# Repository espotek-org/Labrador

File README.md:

# What is it?
The [EspoTek Labrador](http://espotek.com/labrador) is an open-source board that turns your PC, Raspberry Pi, or Android Smartphone into a full-featured electronics lab bench, complete with oscilloscope, signal generator, and more.

This repo hosts all of the software and hardware that makes Labrador possible.

# Tutorial
If you're new to Labrador or oscilloscopes in general, I strongly recommend checking out the fantastic [tutorial series](https://www.wellys.com/posts/courses_electronics/) produced by Lief Koepsel.  It features well-written, rich articles as well as video content that explains everything more clearly than I ever could!

# Getting Started
Binary (executable) versions of the software are available for [download](https://github.com/espotek-org/Labrador/releases) for several platforms.

For the documentation, please visit the [wiki](https://github.com/espotek-org/Labrador/wiki).

## Building from Source
If you're looking to build from source but don't know where to start, Qt Creator is the easiest way to get your toes wet!  
https://www.qt.io/download-open-source/  
When installing, make sure you tick the box to install Qt 5.15 or later.
On Windows, use the MSVC2019 versions - later releases can introduce compatibility issues.

Once it's installed, open `Desktop_Interface/Labrador.pro`, then Clean All -> Run `qmake` -> Build All.

Alternatively, you can build on the command line.  The process will consist of a subset of the commands present in the build scripts in the `.github/workflows/` directory of this repo.  These are run by Github to produce the packages on the [releases page](https://github.com/espotek-org/Labrador/releases), but include app deployment commands that can be skipped for individual users.

Streamlined build scripts for individual Linux (including Raspberry Pi) and macOS users are described in the [Building the desktop interface](https://github.com/espotek-org/Labrador/wiki/Building-from-source#building-the-desktop-interface) section of the wiki.  As shown there, following installation of prerequisite packages, the Linux build simplifies to the following sequence of commands run within the `/Desktop_Interface` directory,
```
QT_SELECT=qt5 qmake
make
sudo make install
```
after which the command `labrador` launches the app.

On macOS:
```
brew install qt@5
brew install libusb
brew install eigen
brew install fftw
echo 'export PATH="/opt/homebrew/opt/qt@5/bin:$PATH"' >> ~/.zshrc

```

To build the AVR software, I use Atmel Studio 7.  Just load up the .atsln located in the `/AVR_Code` directory and push F7.  You can alternatively use open-source command-line AVR tools from GNU if you don't want to install a full IDE.  Instructions for doing so are given in the [Building the firmware](https://github.com/espotek-org/Labrador/wiki/Building-from-source#building-the-firmware) section of the wiki.  If you already have the GNU AVR tools installed, you can jump straight to the [firmware Makefile](https://github.com/espotek-org/Labrador/blob/master/AVR_Code/USB_BULK_TEST/Makefile) and start building.  The wiki includes troubleshooting tips in case you run into issues.

The PCB files can be edited in KiCAD 5.0 or later.

## Using with Nix

A `flake.nix` is provided for NixOS and Nix users:

```bash
# Build the package directly (recommended)
nix build
./result/bin/labrador

# Or enter development shell for hacking
nix develop
cd Desktop_Interface
qmake PREFIX=$PWD/_install
make -j$(nproc)
make install
./_install/bin/labrador
```

**udev rules:** To access the USB device without root, add these rules to your system. On NixOS, add to your `configuration.nix`:
```nix
services.udev.extraRules = ''
  ENV{ID_VENDOR_ID}=="03eb", ENV{ID_MODEL_ID}=="ba94", MODE="0666"
  ENV{ID_VENDOR_ID}=="03eb", ENV{ID_MODEL_ID}=="a000", MODE="0666"
  ENV{ID_VENDOR_ID}=="03eb", ENV{ID_MODEL_ID}=="2fe4", MODE="0666"
'';
```
On other distros, copy `Desktop_Interface/build_linux/69-labrador.rules` to `/etc/udev/rules.d/` and run `sudo udevadm control --reload-rules`. Unplug and replug the device after applying rules.

# Extras
There are community contributed 3D printable cases available at Thingiverse, courtesy of SpaceBex, Bostwickenator and carterw:
* https://www.thingiverse.com/thing:3188243
* https://www.thingiverse.com/thing:4705392
* https://www.thingiverse.com/thing:7400465

Dave Messink has designed [a case that can be laser cut from 3mm plywood](https://github.com/espotek-org/Labrador/files/13813693/Re__Labrador_Case.1.zip).  The [binding posts](https://www.amazon.com/dp/B07YKYP8MN) and [cables](https://www.amazon.com/dp/B08KZGPTLM) he used are from Amazon.  

# Licence
All Desktop software files are licenced under [GNU GPL v3](https://www.gnu.org/licenses/gpl.html).

All Microcontroller software files, with the exception of those provided by Atmel, are licenced under the [3-Clause BSD License](https://opensource.org/licenses/BSD-3-Clause).

All hardware files (schematics, PCB) are licenced under [Creative Commons 4.0 (CC BY-NC-SA)](https://creativecommons.org/licenses/by-nc-sa/4.0/).

# Collaboration
If you want to submit a Pull Request, bug report, or feature request, please feel free to do so here at GitHub.  
If you just want to say hello and remind me that people are actually using my product (or if you just don't want to make a GitHub account), please email admin@espotek.com

Thanks to all.  
~Chris

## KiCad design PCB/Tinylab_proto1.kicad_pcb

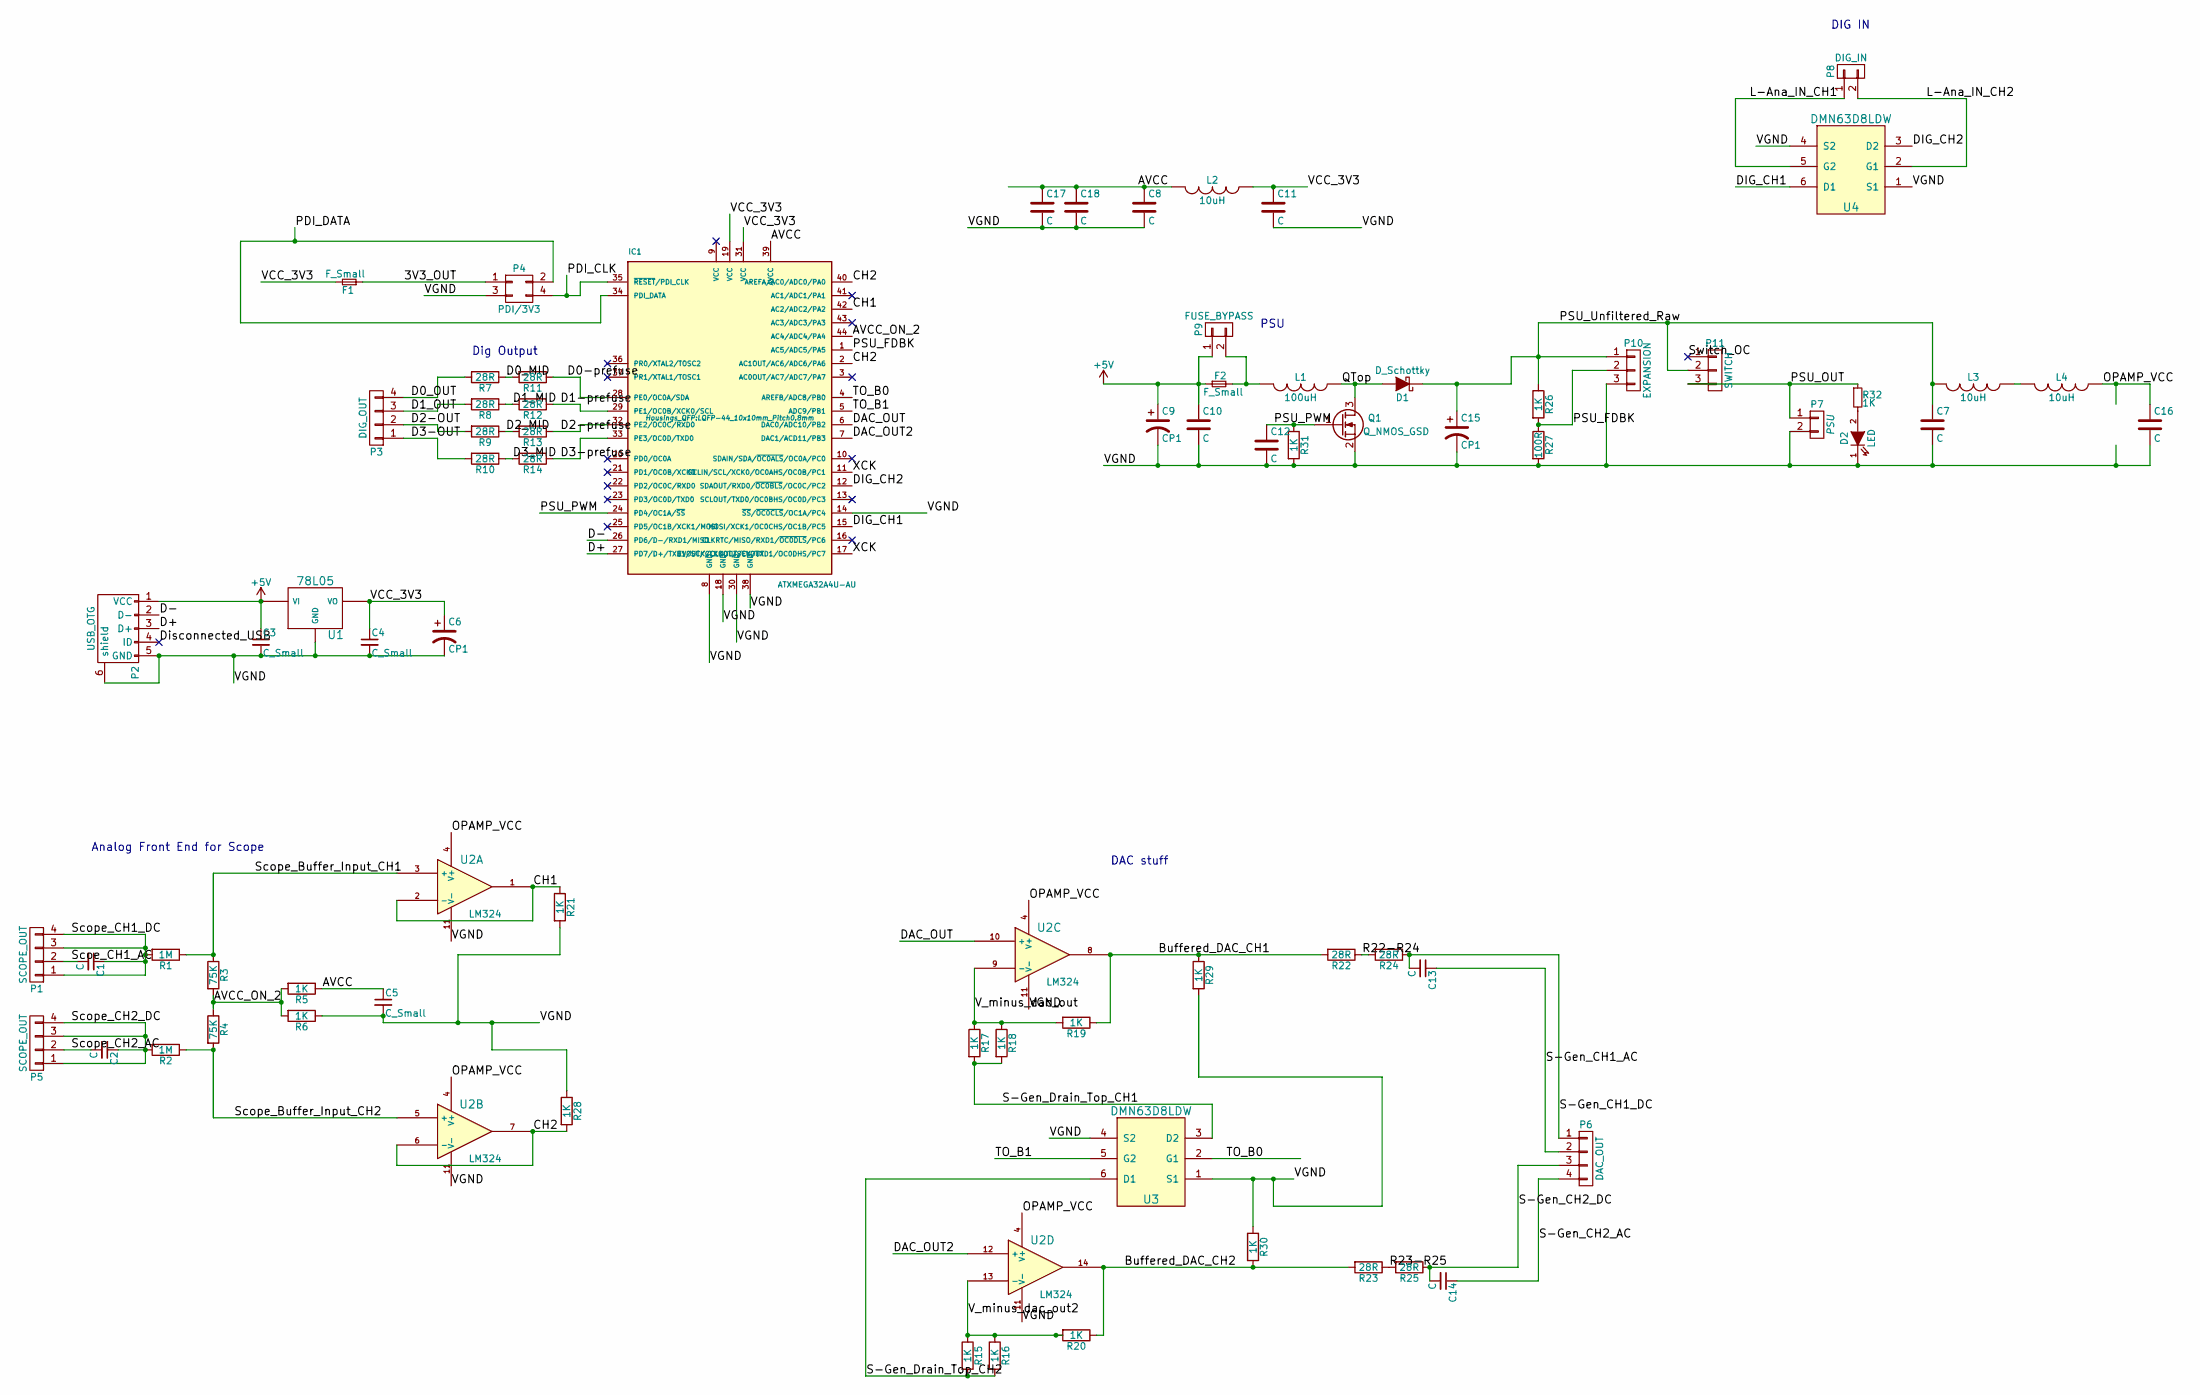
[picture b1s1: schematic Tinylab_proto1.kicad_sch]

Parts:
C1, C2, C7, C8, C10, C11, C12, C13, C14, C16, C17, C18: C; C_0603
C3, C4, C5: C_Small; C_0603
C6, C9, C15: CP1; c_elec_4x5.3
D1: D_Schottky; SMA_Standard
D2: LED; LED_0603
F1, F2: F_Small; C_1210
IC1: ATXMEGA32A4U-AU; LQFP-44_10x10mm_Pitch0.8mm
L1: 100uH; SMALL_INDUCTOR
L2, L3, L4: 10uH; R_1206
P1, P5: SCOPE_OUT; Pin_Header_Straight_1x04
P2: USB_OTG; USB_Micro-B_WIDE
P3: DIG_OUT; Pin_Header_Straight_1x04
P4: PDI/3V3; Pin_Header_Straight_2x02
P6: DAC_OUT; Pin_Header_Straight_1x04
P7: PSU; Pin_Header_Straight_1x02
P8: DIG_IN; Pin_Header_Straight_1x02
P9: FUSE_BYPASS; Pin_Header_Straight_1x02
P10: EXPANSION; Pin_Header_Straight_1x03
P11: SWITCH; Pin_Header_Straight_1x03
Q1: Q_NMOS_GSD; SOT-23-3
R1, R2: 1M; R_0603
R3, R4: 75K; R_0603
R5, R6, R15, R16, R17, R18, R19, R20, R21, R26, R28, R29, R30, R31, R32: 1K; R_0603
R7, R8, R9, R10, R11, R12, R13, R14, R22, R23, R24, R25: 28R; R_0603
R27: 100R; R_0603
U1: 78L05; SOT-23-3
U2: LM324; SOIC-14_3.9x8.7mm_Pitch1.27mm
U3, U4: DMN63D8LDW; SOT-363

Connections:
+5V: C3.1, C9.1, C10.1, F2.1, P2.1 (VCC), P9.1, U1.3 (VI)
/3V3_OUT: F1.1, P4.1
/AVCC: C5.1, C8.1, C17.1, C18.1, IC1.39 (AVCC), L2.2, R5.1
/AVCC_ON_2: IC1.44 (AC4/ADC4/PA4), R3.2, R4.1, R5.2, R6.2
/Buffered_DAC_CH1: R19.1, R22.2, R29.1, U2.8
/Buffered_DAC_CH2: R20.1, R23.2, R30.2, U2.14
/CH1: IC1.42 (AC2/ADC2/PA2), R21.1, U2.1, U2.2 (-)
/CH2: IC1.2 (AC1OUT/AC6/ADC6/PA6), IC1.40 (AREFA/AC0/ADC0/PA0), R28.2, U2.6 (-), U2.7
/D0-prefuse: IC1.28 (PE0/OC0A/SDA), R11.1
/D0_MID: R7.1, R11.2
/D0_OUT: P3.4, R7.2
/D1-prefuse: IC1.29 (PE1/OC0B/XCK0/SCL), R12.1
/D1_MID: R8.1, R12.2
/D1_OUT: P3.3, R8.2
/D2-OUT: P3.2, R9.2
/D2-prefuse: IC1.32 (PE2/OC0C/RXD0), R13.1
/D2_MID: R9.1, R13.2
/D3-OUT: P3.1, R10.2
/D3-prefuse: IC1.33 (PE3/OC0D/TXD0), R14.1
/D3_MID: R10.1, R14.2
/D+: IC1.27 (PD7/D+/TXD1/SCK/CLKOUT/EVOUT), P2.3 (D+)
/D-: IC1.26 (PD6/D-/RXD1/MISO), P2.2 (D-)
/DAC_OUT: IC1.6 (DAC0/ADC10/PB2), U2.10 (+)
/DAC_OUT2: IC1.7 (DAC1/ACD11/PB3), U2.12 (+)
/DIG_CH1: IC1.15 (MOSI/XCK1/OC0CHS/OC1B/PC5), U4.6 (D1)
/DIG_CH2: IC1.12 (SDAOUT/RXD0/~OC0BLS/OC0C/PC2), U4.3 (D2)
/Disconnected_USB: P2.4 (ID)
/L-Ana_IN_CH1: P8.1, U4.5 (G2)
/L-Ana_IN_CH2: P8.2, U4.2 (G1)
/OPAMP_VCC: C16.1, L4.1, U2.4 (V+)
/PDI_CLK: IC1.34 (PDI_DATA), P4.2
/PDI_DATA: IC1.35 (~RESET/PDI_CLK), P4.4
/PSU_FDBK: IC1.1 (AC5/ADC5/PA5), P10.2, R26.2, R27.1
/PSU_OUT: P7.1, P11.3, R32.1
/PSU_PWM: C12.1, IC1.24 (PD4/OC1A/~SS), Q1.1 (G), R31.1
/PSU_Unfiltered_Raw: C7.1, C15.1, D1.1 (K), L3.2, P10.1, P11.2, R26.1
/QTop: D1.2 (A), L1.1, Q1.3 (D)
/R22-R24: R22.1, R24.2
/R23-R25: R23.1, R25.2
/S-Gen_CH1_AC: C13.1, P6.2
/S-Gen_CH1_DC: C13.2, P6.1, R24.1
/S-Gen_CH2_AC: C14.1, P6.4
/S-Gen_CH2_DC: C14.2, P6.3, R25.1
/S-Gen_Drain_Top_CH1: R17.2, R18.2, U3.3 (D2)
/S-Gen_Drain_Top_CH2: R15.2, R16.2, U3.6 (D1)
/Scoe_CH1_AC: C1.2, P1.2
/Scope_Buffer_Input_CH1: R1.1, R3.1, U2.3 (+)
/Scope_Buffer_Input_CH2: R2.1, R4.2, U2.5 (+)
/Scope_CH1_DC: C1.1, P1.1, P1.3, P1.4, R1.2
/Scope_CH2_AC: C2.2, P5.2
/Scope_CH2_DC: C2.1, P5.1, P5.3, P5.4, R2.2
/Switch_OC: P11.1
/TO_B0: IC1.4 (AREFB/ADC8/PB0), U3.2 (G1)
/TO_B1: IC1.5 (ADC9/PB1), U3.5 (G2)
/VCC_3V3: C4.1, C6.1, C11.1, F1.2, IC1.19 (VCC), IC1.31 (VCC), L2.1, U1.2 (VO)
/VGND: C3.2, C4.2, C5.2, C6.2, C7.2, C8.2, C9.2, C10.2, C11.2, C12.2, C15.2, C16.2, C17.2, C18.2, D2.1 (K), IC1.8 (GND), IC1.14 (~SS/~OC0CLS/OC1A/PC4), IC1.18 (GND), IC1.30 (GND), IC1.38 (GND), P2.5 (GND), P2.6 (shield), P4.3, P7.2, P10.3, Q1.2 (S), R6.1, R21.2, R27.2, R28.1, R29.2, R30.1, R31.2, U1.1 (GND), U2.11 (V-), U3.1 (S1), U3.4 (S2), U4.1 (S1), U4.4 (S2)
/V_minus_dac_out: R17.1, R18.1, R19.2, U2.9 (-)
/V_minus_dac_out2: R15.1, R16.1, R20.2, U2.13 (-)
/XCK: IC1.11 (SCLIN/SCL/XCK0/OC0AHS/OC0B/PC1), IC1.17 (EVOUT/CLKOUT/SCK/TXD1/OC0DHS/PC7)
unnamed: D2.2 (A), R32.2
unnamed: F2.2, L1.2, P9.2
unnamed: L3.1, L4.2

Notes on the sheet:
DIG IN
Analog Front End for Scope
Dig Output
DAC stuff
PSU

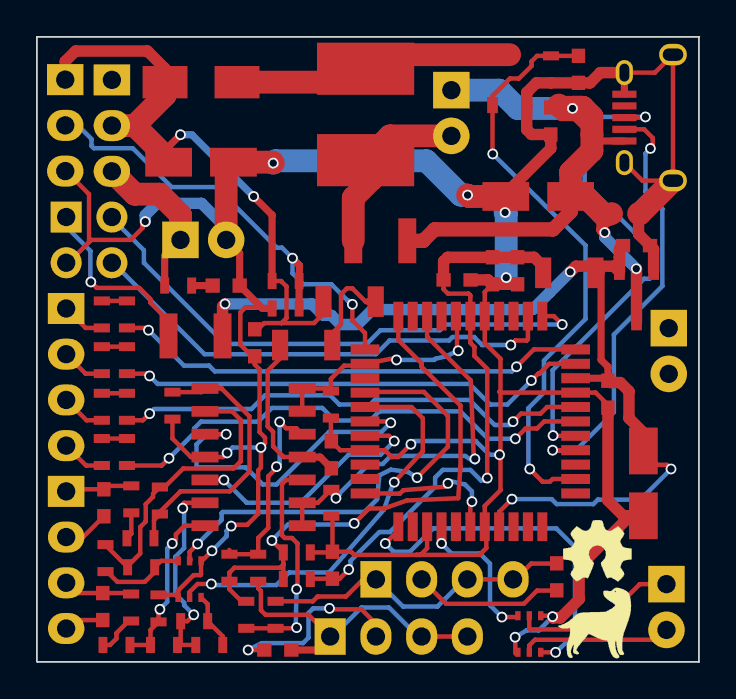
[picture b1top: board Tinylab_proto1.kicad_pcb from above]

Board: 2 copper layers, 36.8 x 34.7 mm, 76 parts (0 on the bottom side), 60 nets.

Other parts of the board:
Main_Logo: LARGE_LOGO; logo175dpi

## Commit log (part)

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2026-01-30 AVR_Code src edits that allow the firmware to be compiled using a Makefile
2026-01-30 draft workflow (.yml and .pro) edits to automate firmware compilation; also removed hard-coded firmware version macros in the Desktop Interface and the firmware
2026-02-06 Enhance USB driver shutdown procedure and improve transfer management
2026-02-06 udd_g_ctrlreq: removed from main.c; removed extern declaration in usb_device.c
2026-02-07 AVR_Code src edits that allow the firmware to be compiled using a Makefile (#404)
    * AVR_Code src edits that allow the firmware to be compiled using a Makefile
    * udd_g_ctrlreq: removed from main.c; removed extern declaration in usb_device.c
2026-02-08 stop-gap hard-coding of firmware version in mac.yml
2026-02-11 Change OSV scanner action to latest version
    Updated the OSV scanner action to use the latest version.
2026-02-11 Change default branch from 'main' to 'master'
2026-02-11 Add workflow_dispatch trigger to OSV scanner
2026-02-11 Change OSV scanner action to latest version of V2 (#408)
    * Change OSV scanner action to latest version
    Updated the OSV scanner action to use the latest version.
    * Change default branch from 'main' to 'master'
    * Add workflow_dispatch trigger to OSV scanner
2026-02-11 Add Dependabot configuration for GitHub Actions
2026-02-15 removed duplicated code by combining conditions in #ifdef directives
2026-02-16 trying to define the avr firmware version using a workflow instead of a repo variable
2026-02-16 -needs- defined at job scope
2026-02-16 typo fix
2026-02-16 workflow file needs at least one job
2026-02-16 job requires runs-on
2026-02-16 job requires a step
2026-02-16 also call avr_ver_def.yml in avr.yml
2026-02-16 had negelected to update 0x0007 to a soft-coded value in a few places
2026-02-16 Restore trailing double spaces in README.md
    The trailing double spaces are intentional Markdown syntax to force line breaks. They were inadvertently removed in commit 3119205.
2026-02-16 Restore trailing double spaces in README.md (#412)
    The trailing double spaces are intentional Markdown syntax to force line breaks. They were inadvertently removed in commit 3119205.
2026-02-19 Enhance USB driver shutdown procedure and improve transfer management (#407)
2026-02-19 Scope range and offset saved on close
2026-02-19 Easier local build on macos ARM
2026-02-19 scope modal dialog has correct range
2026-02-19 Logic Analyzer Offset
2026-02-19 CONFIG += console on windows
2026-02-20 move librador isoCallback mutex positions
2026-02-20 move librador isoCallback mutex positions (#413)
2026-02-22 Fix conditional checks for code signing
2026-02-23 Update mac.yml for workflow triggers and environment variables
    Refactor workflow triggers and clean up environment variable usage.
2026-02-23 Update Android workflow triggers and environment variables
    Added workflow triggers for push and pull request events.
2026-02-23 Modify comment for secrets in linux.yml
    Updated comment regarding secrets for privileged tasks.
2026-02-23 Update GitHub Actions workflow for Windows
2026-02-23 Change AI_KEY to WINDOWS_AdvancedInstaller_KEY
    Updated the workflow to use a new secret for Advanced Installer registration.
2026-02-23 Update linux.yml
    remove invalid tab
2026-02-23 Add permissions section to Windows workflow
2026-02-23 Update firmware hex files in Labrador.aip
    Removed obsolete firmware hex files and added new ones for labrafirm.
2026-02-23 Remove duplicate labrafirm hex files from installer
2026-02-25 Simplify and standardize QT project file and Windows installer (#422)
    * Use identical logic for firmware deployment for all OSes
    simplify logic to avoid bugs caused by inconsistencies/differences
    * Update firmware hex files in Labrador.aip
    Removed obsolete firmware hex files and added new ones for labrafirm.
    * Include Windows firmware update files in Labrador.pro
    Add Windows-specific firmware update files to the project.
2026-02-25 CONFIG += console on windows (#424)
2026-03-04 Add graceful USB driver shutdown and reinit handling
    When reinitializing USB on Windows, MainWindow now triggers a driver shutdown if the driver is connected and waits for a shutdownComplete signal before running reinitUsbStage2. The winUsbDriver gaine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
2026-03-04 Platform-specific pipeID and winusb cleanup
    Make pipeID handling platform-aware and tidy winusb behavior. In the USB generic driver, the pipeID array is now conditionally sized (NUM_ISO_ENDPOINTS on Windows, legacy 3 otherwise) and debug outpu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
2026-03-05 Ignore Desktop_Interface test/build/tools
    Add Desktop_Interface/run_test_win, Desktop_Interface/build_test_win_custom, and Desktop_Interface/tools to .gitignore so generated test/build artifacts are not tracked. Keeps the existing Desktop_In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
2026-03-05 updated USB descriptor
2026-03-05 USB stack should be spec-compliant
2026-03-06 bmAttributes set to 0x05
2026-03-08 Build and static-link libdfuprog
2026-03-08 Recursive submodule checkout
2026-03-08 Remove another dynamic lib hack
2026-03-09 new lidfuprog on macos
2026-03-10 PCB update to swap incorrect labels
    Labels for nets PDI_CLK and PDI_DATA swapped to match ATxmega32A4U pinout. saved as Kicad 9.0 files
2026-03-11 Download submodules in the bootstrap script
2026-03-11 Build and static-link libdfuprog (#428)
2026-03-11 Remove PCB label update from PR
2026-03-11 Restore .gitignore to match upstream master
2026-03-13 restores widget enabled/hidden settings on reload
2026-03-14 Stack Allocated QSettings
2026-03-17 Re-add --no-undefined to Android builds
2026-03-17 Copy dfu_make_idle as a workaround
2026-03-18 Remove failing/disabled dependabot workflow
    This workflow causes a build failure in each fork.
    Automated dependency updates or PRs to that effect are undesired.
2026-03-20 removed duplicated code by combining conditions in #ifdef directives
    Refactor platform-specific USB reinitialization logic and update debug message.
2026-03-22 preventing mode 5 from being sent to the board
2026-03-23 Firmware makefile cleanup
    Remove unused/empty variables.
    Replace AVRDIR with CROSS_COMPILE.
    Add line breaks for readability.
    Don't hide the compiler command line.
    Use pattern rules and pattern substitution to avoid duplication.
    Mark all phony targets as phony.
2026-03-23 Name the generated files to match existing conventions
2026-03-23 Normalize line endings and permissions in generated files
2026-03-23 Skip generating .srec and .eep files by default
2026-03-24 revisit d7bdf69: preventing mode 5 from being sent to the board (#439)
2026-03-24 Drop 0x prefix
2026-03-27 Prerequisite fixes
    Listing files by name as targets prevents make from deleting them as
    intermediate. Fixes the problem where running `make` a second time will
    rebuild everything it just deleted, since it now finds a mention of the
    file in a .d file.
    Add a dependency on Makefile, so that objects get rebuilt if anything in
    the Makefile changes.
2026-03-27 Automatically add -D/-I to defines/includes
2026-03-27 Add a 'mostlyclean' target
2026-03-27 Update .gitignore with firmware file patterns
2026-03-27 Define FIRMWARE_VERSION_ID from the Makefile
2026-03-27 Update wiki link and drop AVRDIR reference
2026-03-27 Document the mostlyclean target
2026-04-17 files for imgui android app
2026-04-17 CMakeLists for libdfuprog for imgui-android build
2026-04-17 added submodules
2026-04-17 added PLATFORM_ANDROID guards to librador - usbcallhandler.cpp
2026-04-17 rename
2026-04-17 name updates
2026-04-17 make all logging macros LIBRADOR_LOG
2026-04-17 more #ifdef PLATFORM_ANDROID wrapping
2026-04-17 revised android.yml so that it builds the imgui app
2026-04-17 android.yml indentation edit
2026-04-17 android.yml apk directory fix?
2026-04-17 move android-specific files from Desktop_Interface to Android_App/legacy
2026-04-17 remove code wrapped by '#ifdef PLATFORM_ANDROID' in Desktop_Interface; remove '#ifndef PLATFORM_ANDROID' directives as well
2026-04-17 new icon files
2026-04-18 remove more default Android icons
2026-04-18 backup icon files
2026-04-18 now backed up the correct icon.png
2026-04-21 appropriate precision for the reference line legend; also a new greek delta
2026-04-21 android: clamping and appropriate precision for the axis limit selector pop-ups
2026-04-21 android: streamline 712350f
2026-04-21 android: tweaks to 002a526
2026-04-21 android: float->double for axis limits
2026-04-21 float->double for reference line values
2026-04-23 bump up the minimum android version number in the continuous release blurb
2026-04-30 android: disable row-col tiling in landscape mode if there are only singlet-width tiles
2026-05-05 android: remove unneeded SDL files from cmakelists source sets list
2026-05-07 Google Play app
2026-05-08 Android: back up Play store graphics
2026-05-18 remove #include of legacy android file
2026-05-24 Android: started doing daq
2026-05-25 Android: basic daq ui tile
2026-05-25 Android: daq UI mostly done; data conversion code for daq is compiling; 'save to file' code for daq hasn't been started
2026-05-26 Android: instacrashing
2026-05-26 Android: file creation for daq is working
2026-05-27 Android: analog daq is functional
2026-05-27 Android: prevent inadvertent presses to other widgets when deacivating an 'Input' widget
2026-05-27 Android: imgui submodule commit update
2026-05-28 Android: tweaks to daq
2026-05-29 Android: for daq, get required WRITE_EXTERNAL_STORAGE permission on sdk <= 28 (Android 9)
2026-05-29 Android: ADC units for scope daq appears to be working
2026-05-29 Android: functional daq permission request
2026-05-29 Android: readability
2026-05-29 Android: don't allow '/' in daq filename
2026-05-29 Android: clean up daq fn call chain
2026-05-29 Android: change # digits for volts daq
2026-05-30 Android: improved daq options parsing
2026-05-30 Android: use inputs_ui instance to determine sampling rate
2026-05-30 Android: improve validation of daq unit selection
2026-05-30 Android: make iso_thread_active an atomic bool; remove mutex protections
2026-05-30 Android: simplify code for uart options combo boxes
2026-05-30 Android: enable librador_daq usb/api init checks
2026-05-30 Android: glyphs for daq
2026-06-10 Android/librador: correct the buffer traversal direction for ADC daq
2026-06-11 optimize timing integrity in two-channel scope mode: disable sig. gen ch2 and change the ch1 dma trigger to adc ch2
2026-06-16 Android: resize daq glyphs
2026-06-16 Android: round daq time to ms
2026-06-16 Android: fix kSa/s vs Sa/s error for daq
2026-06-17 Android: improve DAQ user interface: print 'Saved' when DAQ finishes, disable Start/End buttons if Record=None, change widget spacing
2026-06-17 Android/librador: fix bug that causes a sample to be overwritten when addVector is called
2026-06-17 Android: fix 'unsigned char' type issue for DAQ of adc values
2026-06-17 Android: disable daq Begin/End buttons if duration=0
2026-06-17 Android: start ensuring that the tiling system works for the new DAQ tile
2026-06-17 Android: try to do away with the width adjustments for thin phones
2026-06-17 Android: tweak tile widths as well as the 'File path' tooltip behavior
2026-06-18 Android: remove comments
2026-06-18 Android: change line wrapping for daq 'File path' tooltip
2026-06-18 Android: compactify daq tile width-wise
2026-06-18 Android: simplified logic for row-col tiling
2026-06-18 Android: streamline tiling code
2026-06-19 Android: adapt size of invisible button for tile selector popup as user scrolls
2026-06-19 Android: chronological print order for daq
2026-06-19 Android: DAQ ui tweaks
2026-06-19 Android: fix DAQ bit sample rate vs volts sample rate bug; also add a space after printing a bit
2026-06-19 Android: improve CH A/B daq time sync using mutex
2026-06-19 Android: make adc daq output in chronological order
2026-06-19 Android: prevent settings panel invisible button from preventing disabling of scroll bar
2026-06-20 Android: fix daq tile layout bug
